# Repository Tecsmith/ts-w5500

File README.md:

# ts-w5500

```txt
    ░▒▓▓▓▓▓▓▓▓▓▓▓▓▓▓▓▓▓▓▓▓▓▓▓▓▓▓▓▓▓▓▓▓▓▓▓▓▓▓▓▓▓▓▓▓▓▓▓▓▓▓▓▒░
    ░▒▓                                                 ▓▒░
    ░▒▓          Placeholder for future project         ▓▒░
    ░▒▓                                                 ▓▒░
    ░▒▓▓▓▓▓▓▓▓▓▓▓▓▓▓▓▓▓▓▓▓▓▓▓▓▓▓▓▓▓▓▓▓▓▓▓▓▓▓▓▓▓▓▓▓▓▓▓▓▓▓▓▒░

                      ⚠️ ⚠️ DO NOT BUILD ⚠️ ⚠️

```

Redo of the common W5500 module, this time with breakouts for a PoE module.

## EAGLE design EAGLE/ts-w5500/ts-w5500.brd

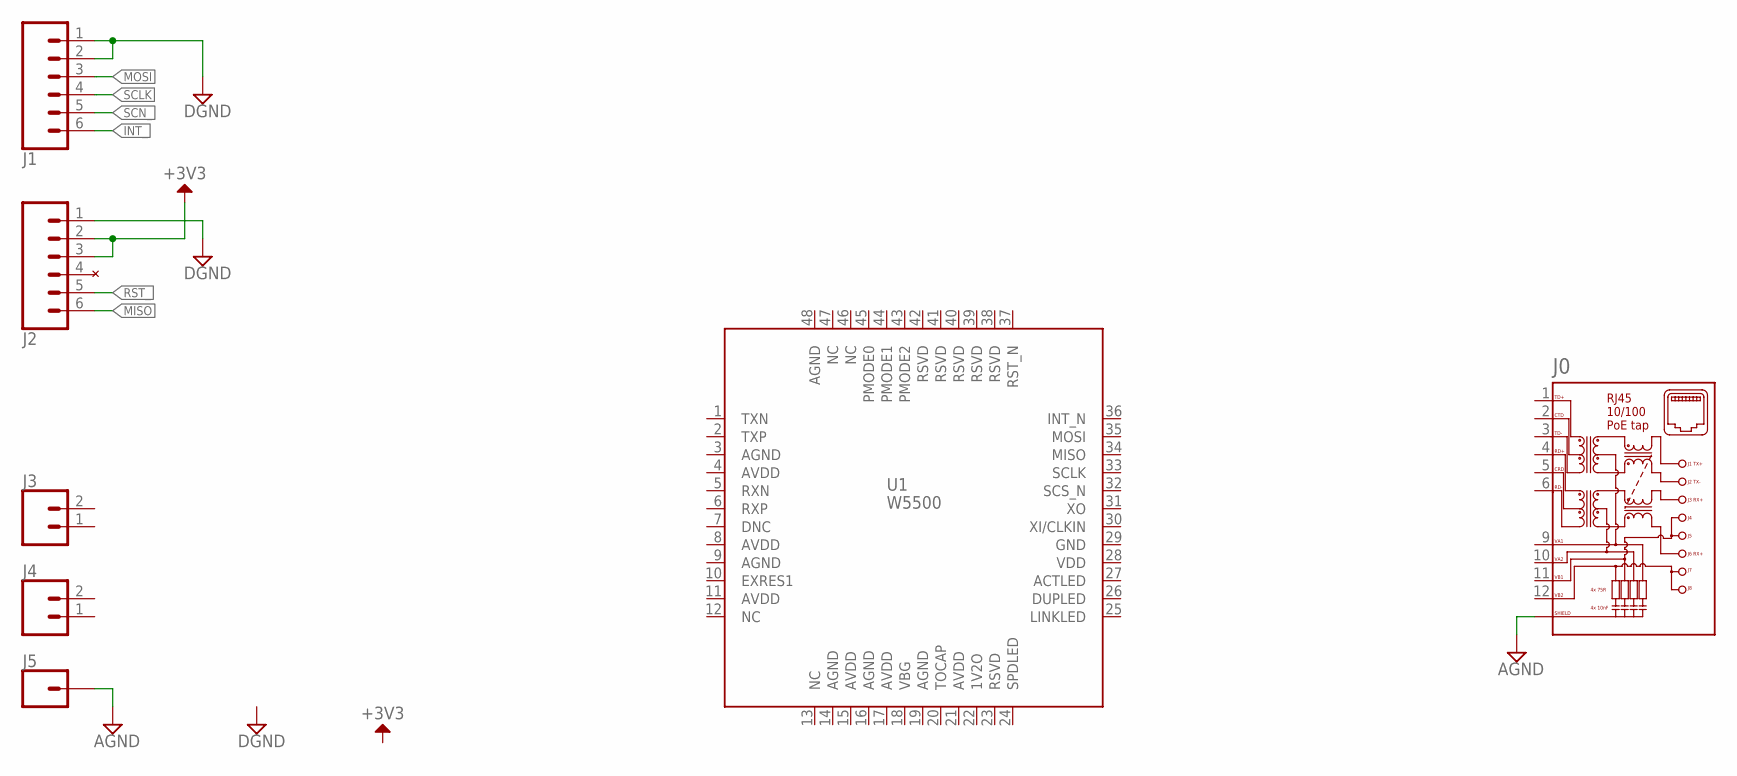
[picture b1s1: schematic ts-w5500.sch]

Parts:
J0: 7498210003; SMD_7498210003
J1, J2: CONN_06NO_SILK_NO_POP; 1X06_NO_SILK
J3, J4: CONN_021X02_NO_SILK; 1X02_NO_SILK
J5: CONN_01; 1X01
U1: W5500

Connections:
+3V3: J2.2, J2.3
AGND: J0.13 (SHIELD), J0.14 (SHIELD), J5.1
DGND: J1.1, J1.2, J2.1
INT_: J1.6
MISO: J2.6
MOSI: J1.3
RST_: J2.5
SCLK: J1.4
SCN_: J1.5

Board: 2 copper layers, 7 parts (2 on the bottom side), 3 nets, no tracks yet.

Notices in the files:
parts and their libraries:
SparkFun-Connectors: Licensing: Creative Commons ShareAlike 4.0 International - https://creativecommons.org/licenses/by-sa/4.0
